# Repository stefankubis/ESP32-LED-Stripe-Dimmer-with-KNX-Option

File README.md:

# ESP32 LED Stripe Dimmer with KNX Option
ESP32 LED Stripe Dimmer with KNX Option

Created with KiCad

# Part List

| Qty | Type | Reference | 
| --- | ---- | --------- | 
| 1 | Voltage Regulator L7805 | U1 |
| 1 | ESP32-DEVKITC | U2 |
| 12 | Transistor 2N2222A | Q1, Q2, Q4, Q5, Q7, Q8, Q10, Q11, Q13, Q14, Q16, Q17 |
| 6 | Transistor IRFZ44N | Q3, Q6, Q9, Q12, Q15, Q18 |
| 12 | Resistor 10k | R1, R2, R3, R6, R7, R8, R10, R11, R12, R14, R15, R16, R18, R19, R20, R22, R23, R24 |  
| 6 | Resistor 1k | R4, R5, R9, R13, R17, R21 |  
| 1 |Capacitor 0.1μF | C1 |
| 1 | Screw Terminal 01x07 | J1 |
| 1 | Screw Terminal 01x02 | J2 |
| 1 | Connector Pin Header 02x05 for KNX (optional) | J3 |
| 1 | Screw Terminal 01x08 | J4 |
| 1 | Connector Pin Header 01x03 | JP1 |
| 1 | Jumper | JP1 |

# KNX Option
For KNX Add Siemens 5WG1117-2AB12 Module to Connector

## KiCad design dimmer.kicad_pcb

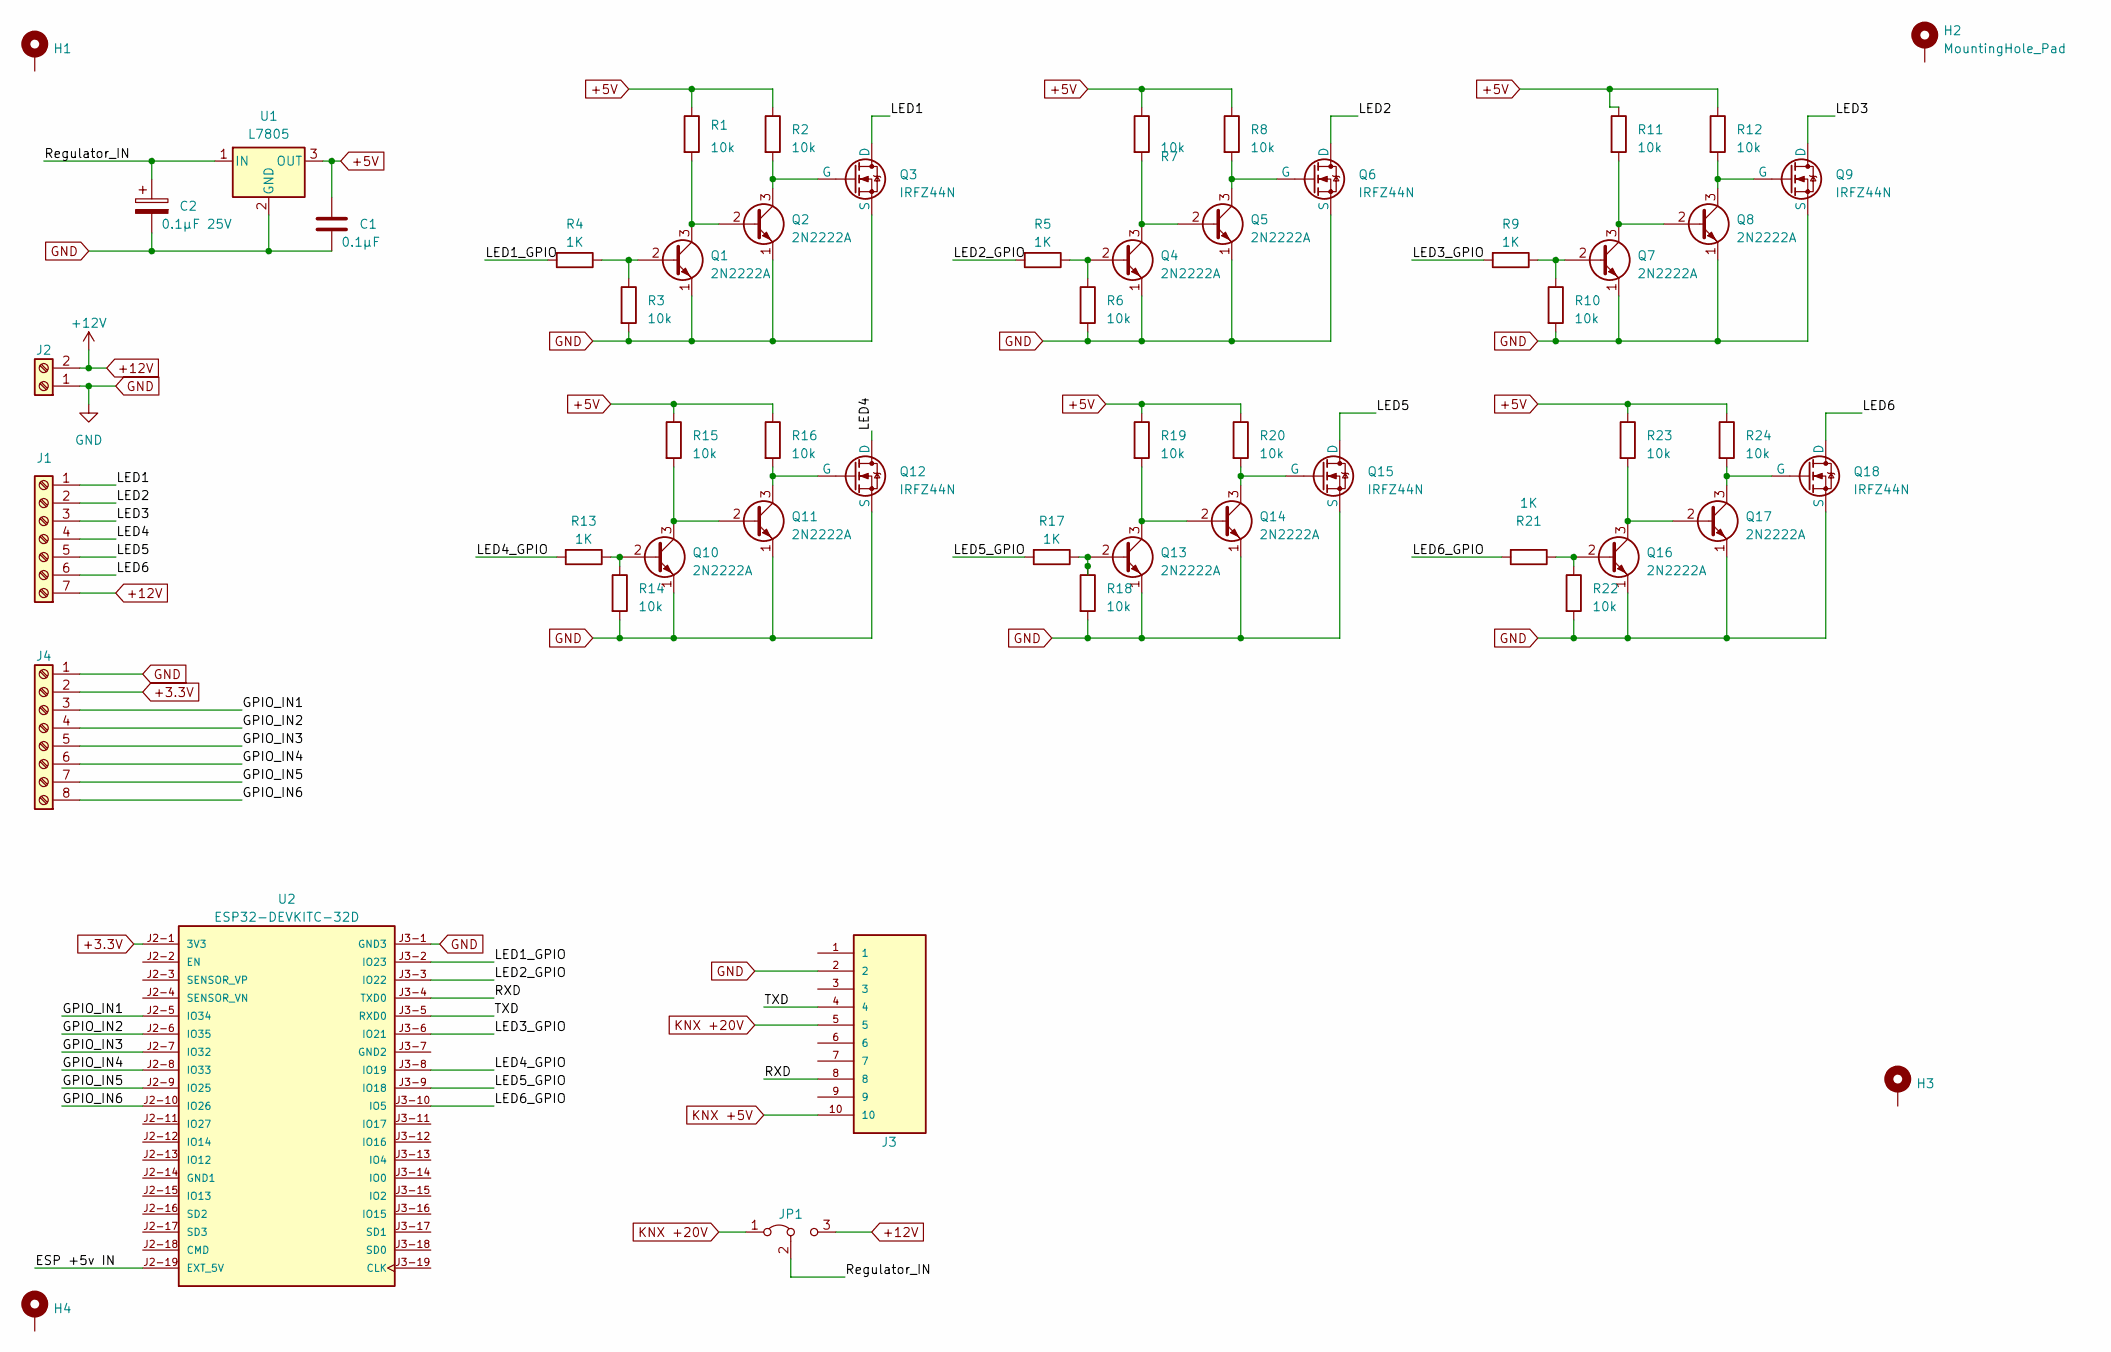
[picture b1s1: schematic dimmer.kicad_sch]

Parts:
C1: 0.1μF; CP_Radial_D4.0mm_P1.50mm
C2: 0.1μF 25V; CP_Radial_D18.0mm_P7.50mm
H1, H2, H3, H4: MountingHole_Pad; MountingHole_3mm_Pad
J1: Screw_Terminal_01x07; Altech_AK300_1x07_P5.00mm_45-Degree
J2: Screw_Terminal_01x02; TerminalBlock_Altech_AK300-2_P5.00mm
J3: KNX-IN; PinHeader_2x05_P2.54mm_Vertical
J4: Screw_Terminal_01x08; Altech_AK300_1x08_P5.00mm_45-Degree
JP1: Jumper_3_Bridged12; PinHeader_1x03_P2.54mm_Vertical
Q1, Q2, Q4, Q5, Q7, Q8, Q10, Q11, Q13, Q14, Q16, Q17: 2N2222A; TO-92_Inline
Q3, Q6, Q9, Q12, Q15, Q18: IRFZ44N; TO-220-3_Vertical
R1, R2, R3, R6, R7, R8, R10, R11, R12, R14, R15, R16, R18, R19, R20, R22, R23, R24: 10k; R_Axial_DIN0411_L9.9mm_D3.6mm_P12.70mm_Horizontal
R4, R5, R9, R13, R17, R21: 1K; R_Axial_DIN0411_L9.9mm_D3.6mm_P12.70mm_Horizontal
U1: L7805; TO-220-3_Vertical
U2: ESP32-DEVKITC-32D; MODULE_ESP32-DEVKITC-32D; PARTREV V4

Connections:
+3.3V: J4.2, U2.J2-1 (3V3)
+5V: C1.1, R1.1, R2.1, R7.1, R8.1, R11.1, R12.1, R15.1, R16.1, R19.1, R20.1, R23.1, R24.1, U1.3 (OUT)
+12V: J1.7, J2.2, JP1.3 (B)
/ESP +5v IN: U2.J2-19 (EXT_5V)
/GPIO_IN1: J4.3, U2.J2-5 (IO34)
/GPIO_IN2: J4.4, U2.J2-6 (IO35)
/GPIO_IN3: J4.5, U2.J2-7 (IO32)
/GPIO_IN4: J4.6, U2.J2-8 (IO33)
/GPIO_IN5: J4.7, U2.J2-9 (IO25)
/GPIO_IN6: J4.8, U2.J2-10 (IO26)
/LED1: J1.1, Q3.2 (D)
/LED1_GPIO: R4.2, U2.J3-2 (IO23)
/LED2: J1.2, Q6.2 (D)
/LED2_GPIO: R5.2, U2.J3-3 (IO22)
/LED3: J1.3 (Pin_4), Q9.2 (D)
/LED3_GPIO: R9.2, U2.J3-6 (IO21)
/LED4: J1.4, Q12.2 (D)
/LED4_GPIO: R13.2, U2.J3-8 (IO19)
/LED5: J1.5, Q15.2 (D)
/LED5_GPIO: R17.2, U2.J3-9 (IO18)
/LED6: J1.6, Q18.2 (D)
/LED6_GPIO: R21.2, U2.J3-10 (IO5)
/RXD: J3.8, U2.J3-4 (TXD0)
/Regulator_IN: C2.1, JP1.2 (C), U1.1 (IN)
/TXD: J3.4, U2.J3-5 (RXD0)
GND: C1.2, C2.2, J2.1, J3.2, J4.1, Q1.1 (E), Q2.1 (E), Q3.3 (S), Q4.1 (E), Q5.1 (E), Q6.3 (S), Q7.1 (E), Q8.1 (E), Q9.3 (S), Q10.1 (E), Q11.1 (E), Q12.3 (S), Q13.1 (E), Q14.1 (E), Q15.3 (S), Q16.1 (E), Q17.1 (E), Q18.3 (S), R3.2, R6.2, R10.2, R14.2, R18.2, R22.2, U1.2 (GND), U2.J3-1 (GND3)
KNX +5V: J3.10
KNX +20V: J3.5, JP1.1 (A)
unnamed: Q1.2 (B), R3.1, R4.1
unnamed: Q1.3 (C), Q2.2 (B), R1.2
unnamed: Q2.3 (C), Q3.1 (G), R2.2
unnamed: Q4.2 (B), R5.1, R6.1
unnamed: Q4.3 (C), Q5.2 (B), R7.2
unnamed: Q5.3 (C), Q6.1 (G), R8.2
unnamed: Q7.2 (B), R9.1, R10.1
unnamed: Q7.3 (C), Q8.2 (B), R11.2
unnamed: Q8.3 (C), Q9.1 (G), R12.2
unnamed: Q10.2 (B), R13.1, R14.1
unnamed: Q10.3 (C), Q11.2 (B), R15.2
unnamed: Q11.3 (C), Q12.1 (G), R16.2
unnamed: Q13.2 (B), R17.1, R18.1
unnamed: Q13.3 (C), Q14.2 (B), R19.2
unnamed: Q14.3 (C), Q15.1 (G), R20.2
unnamed: Q16.2 (B), R21.1, R22.1
unnamed: Q16.3 (C), Q17.2 (B), R23.2
unnamed: Q17.3 (C), Q18.1 (G), R24.2

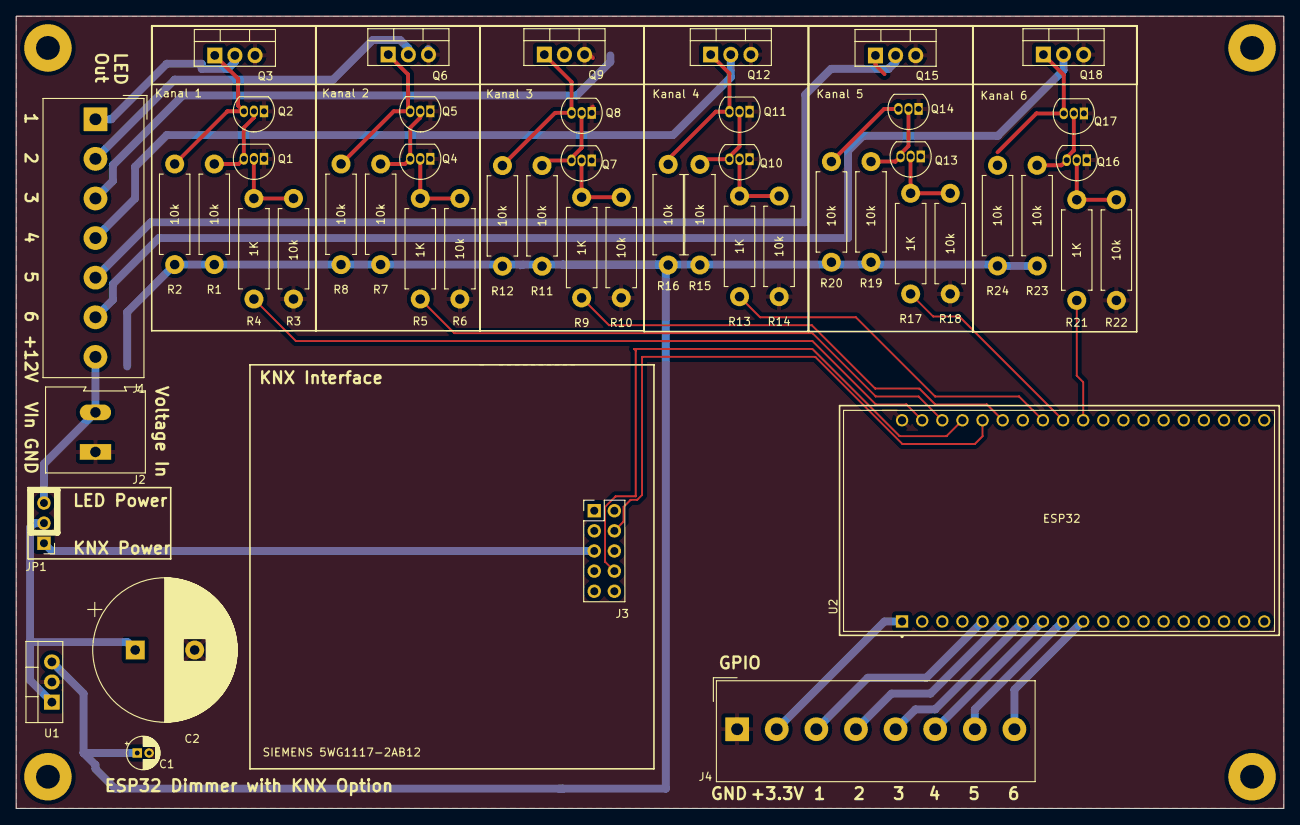
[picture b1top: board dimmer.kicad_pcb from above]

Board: 2 copper layers, 160.0 x 100.0 mm, 55 parts (0 on the bottom side), 44 nets.

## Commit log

2023-04-20 Added PCB Image
2023-04-20 div changes
2023-04-20 updated circuit board image
2023-04-20 Cleanup Schematics
2023-04-20 div cleanups
2023-04-20 div updates
